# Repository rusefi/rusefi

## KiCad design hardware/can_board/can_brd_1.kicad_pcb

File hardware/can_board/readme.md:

CAN using SN65HVD230

[Forum thread](http://rusefi.com/forum/viewtopic.php?f=4&t=353)

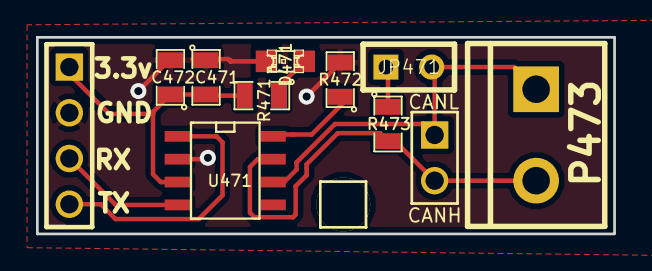
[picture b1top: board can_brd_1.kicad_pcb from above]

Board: 2 copper layers, 32.1 x 10.9 mm, 13 parts (1 on the bottom side), 9 nets.

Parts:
C471: .1uF; SM0805
C472: 4.7uF; SM0805
D471: RED; LED-0805_A
G471: LOGO; LOGO_F
JP471: JUMPER; JUMPER-2
M471: CONN_1; PIN_ARRAY_1
P471: CONN_4; PIN_ARRAY_4x1
P472: CONN_2; PIN_ARRAY_2_A
P473: CONN_2; bornier2
R471: 1k; SM0805
R472: 10k; SM0805
R473: 120; SM0805
U471: SN65HVD230; SO8E

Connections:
/3.3V: C471.2, C472.1, P471.1, R471.2, U471.3
/CANH: P472.2, P473.2, R473.2, U471.7
/CANL: JP471.2, P472.1, P473.1, U471.6
/CAN_RX: P471.3, U471.4
/CAN_TX: P471.4, U471.1
GND: C471.1, C472.2, D471.2, P471.2, R472.2, U471.2
unnamed: D471.1, R471.1
unnamed: JP471.1, R473.1
unnamed: R472.1, U471.8

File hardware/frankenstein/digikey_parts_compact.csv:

### this file was generated by rusEfi bom_builder on Sat Feb 22 11:01:39 CST 2014
### 292 components in 2047 lines of frankenstein.cmp
### 65 kinds of components in input file
### 9 entries in BOM dictionary bom_dictionary_digikey.csv
### 2 entries in ignore list
### no BOM record for 1pin_CONN_1
### no BOM record for LED-0805_GREEN
### no BOM record for LED-0805_LED
### no BOM record for LED-0805_RED
### no BOM record for LED-1206_LED
### no BOM record for MICRO-SDCARD-CONNECTOR-3300060P1_MICRO-SDCARD-CONNECTOR-3300060P1
### no BOM record for OSTVN06A150_CONN_6
### no BOM record for PIN_ARRAY-6X1_CONN_6
### no BOM record for PIN_ARRAY_10X2_CONN_10X2
### no BOM record for PIN_ARRAY_10X2_M_CONN_10X2
### no BOM record for PIN_ARRAY_1_CONN_1
### no BOM record for PIN_ARRAY_2X1_CONN_2
### no BOM record for PIN_ARRAY_2_A_CONN_2
### no BOM record for PIN_ARRAY_2_A_JUMPER
### no BOM record for PIN_ARRAY_3X1_CONN_3
### no BOM record for PIN_ARRAY_3_A_CONN_3
### no BOM record for PIN_ARRAY_4x1_CONN_4
### no BOM record for PIN_ARRAY_5x2_CONN_5X2
### no BOM record for SIL-16_3.5MM_CONN_16
### no BOM record for SIL-2_0R
### no BOM record for SIL-2_CONN_2
### no BOM record for SIL-2_DIODE
### no BOM record for SIL-2_JUMPER
### no BOM record for SIL-2_OPT
### no BOM record for SIL-2_TEST
### no BOM record for SM0805_.1uF
### no BOM record for SM0805_0.01uF
### no BOM record for SM0805_0.1uF
### no BOM record for SM0805_100
### no BOM record for SM0805_1000pF
### no BOM record for SM0805_10K
### no BOM record for SM0805_10k
### no BOM record for SM0805_10uF
### no BOM record for SM0805_120
### no BOM record for SM0805_1500
### no BOM record for SM0805_1K
### no BOM record for SM0805_1M
### no BOM record for SM0805_1uF
### no BOM record for SM0805_20K
### no BOM record for SM0805_2700
### no BOM record for SM0805_4.7uF
### no BOM record for SM0805_4700pF
### no BOM record for SM0805_47pF
### no BOM record for SM0805_500K
### no BOM record for SM0805_5k
### no BOM record for SM0805_LED
### no BOM record for SM1206_LED
### no BOM record for SOD-123_DIODE
### no BOM record for bornier3_CONN_3
### no BOM record for pin_array_10x2_CONN_10X2
### no BOM record for pin_array_3x2_CONN_3X2
### no BOM record for pin_array_4x2_CONN_4X2
### no BOM record for sot23_DOUBLE_SCHOTTKY
### no BOM record for uMAX-uSOP_10_MAX9939




1,670-1190-1-ND,mini USB socket
4,P1.0KACT-ND,some reference
12,P20.0CCT-ND,driver current limiting
1,296-11654-1-ND,CAN driver
12,497-11082-1-ND,12A low-side MOSFET
1,MAX9926UAEE+TCT-ND,VR chip
3,TC4427AVOA-ND,1.5A dual driver
3,497-4943-1-ND,quad op-amp
1,768-1007-1-ND,USB TTL chip

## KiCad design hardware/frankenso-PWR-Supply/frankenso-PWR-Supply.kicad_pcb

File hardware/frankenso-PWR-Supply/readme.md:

https://rusefi.com/forum/viewtopic.php?f=4&t=394

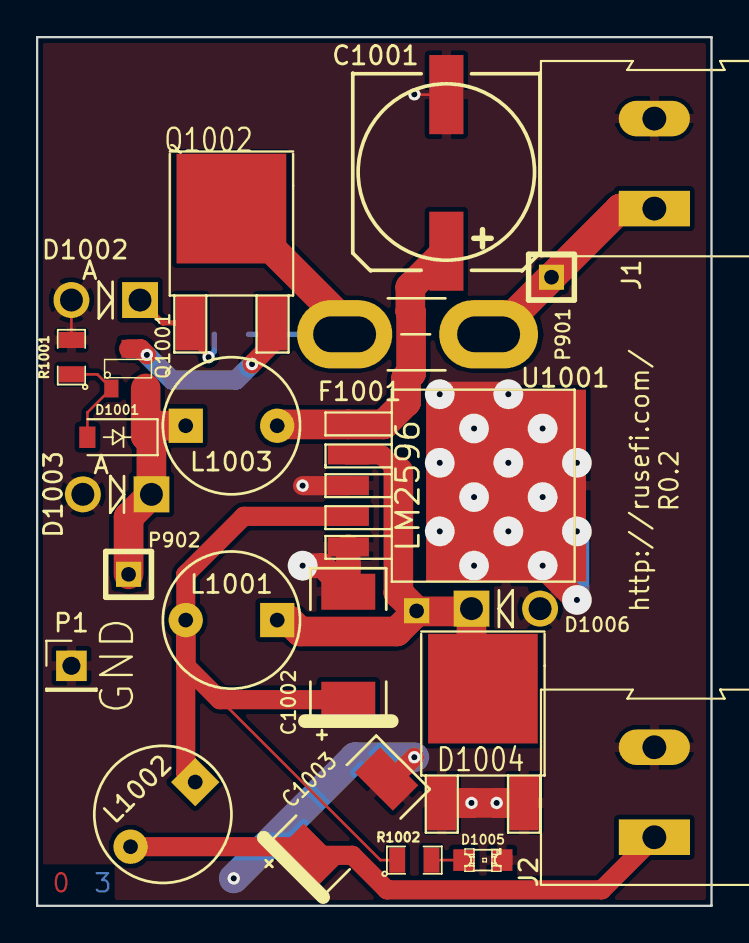
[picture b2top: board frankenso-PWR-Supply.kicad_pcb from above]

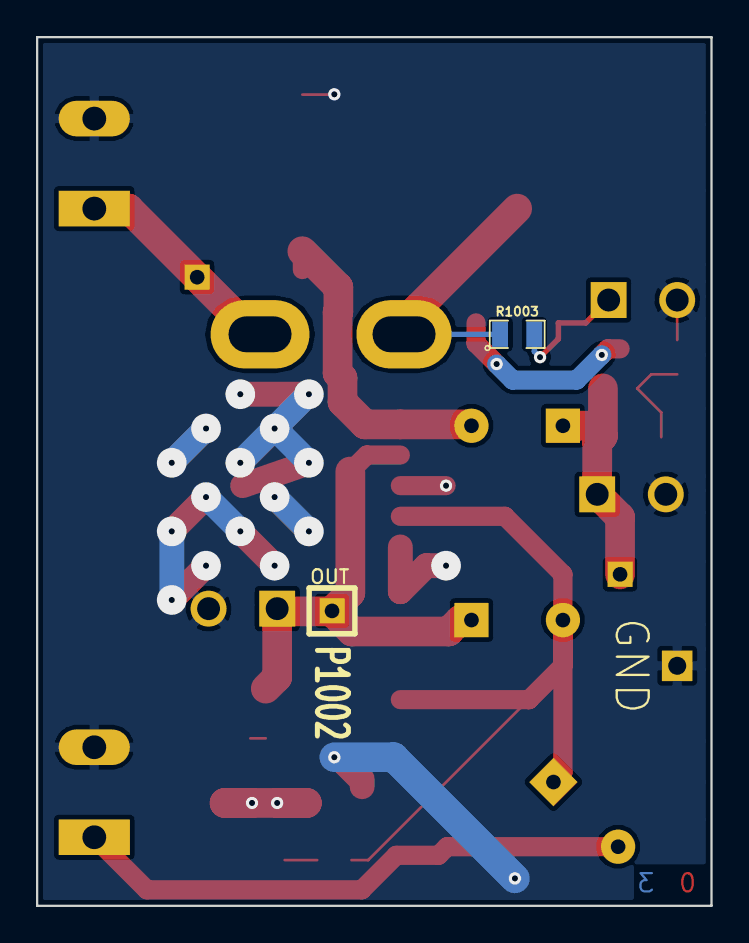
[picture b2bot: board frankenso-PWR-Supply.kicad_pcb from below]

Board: 2 copper layers, 37.5 x 48.3 mm, 25 parts (2 on the bottom side), 12 nets.

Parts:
C1001: 330uF 35V; SMDSVP10
C1002, C1003: 220uF 16V; SM2512
D1001: 7.5V; D_SOD-123
D1002: 17V; Diode_DO-41_SOD81_Vertical_AnodeUp
D1003: 24V; Diode_DO-41_SOD81_Vertical_AnodeUp
D1004: DIODESCH; DPAK2
D1005: LED-grn; LED-0805
D1006: DIODESCH; Diode_DO-41_SOD81_Vertical_AnodeUp
F1001: 1.5A; BladeFuse-Mini
J1, J2: Screw_Terminal_1x02; AK300-2
L1001, L1002, L1003: 68uH; INDUCTOR_V
P1: CONN_1; Pin_Header_Straight_1x01_Pitch2.54mm
P901, P902, P1002: CONN_1; SIL-1
Q1001: 20V; SOT23
Q1002: 200V; DPAK2
R1001: 39k; SM0805
R1002: 1k; SM0805
R1003: 100k; SM0805
U1001: LM2596; DPAK5

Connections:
/5V-REG: C1003.1, J2.1, L1002.2
/FB: C1002.1, L1001.2, L1002.1, R1002.1, U1001.4
/OUT: D1004.2, D1006.1, L1001.1, P1002.1, U1001.2
/VBAT: C1001.1, L1003.2, U1001.1
/Vf: F1001.2, Q1002.2, R1003.1
/Vin: F1001.1, J1.1, P901.1
/Vs1: D1002.1, Q1002.1, R1003.2
/Vs2: Q1001.3, Q1002.3
GND: C1001.2, C1002.2, C1003.2, D1002.2, D1003.2, D1004.1, D1004.3, D1005.2, D1006.2, J1.2, J2.2, P1.1, R1001.2, U1001.3, U1001.5
unnamed: D1001.1, D1003.1, L1003.1, P902.1, Q1001.2
unnamed: D1001.2, Q1001.1, R1001.1
unnamed: D1005.1, R1002.2

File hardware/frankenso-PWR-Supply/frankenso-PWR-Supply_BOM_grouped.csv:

Reference, Quantity, Value, Footprint, Datasheet, MFG,MFG#, VEND1,VEND1#, VEND2,VEND2#, vend1,vend1#, Field4, Field5
C1001 ,1,330uF 35V,SMDSVP10,,unitedchem,EMVY350ADA331MJA0G,DIGI,565-2479-1-ND,,,,
C1002 C1003 ,2,220uF 16V,SM2512,,kemet,T491D227K016AT,DIGI,399-10429-1-ND,sky-macau.com,8702041755,,,
D1001 ,1,7.5V,Diodes_SMD:D_SOD-123,,diodesinc,BZT52C7V5-7-F,DIGI,BZT52C7V5-FDICT-ND,sky-macau.com,5633100308,,,
D1002 ,1,17V,Diode_DO-41_SOD81_Vertical_AnodeUp,,FAIRCHILD,1N5247B,DIGI,1N5247B-ND, ,,,
D1003 ,1,24V,Diode_DO-41_SOD81_Vertical_AnodeUp,,MicroComercial,1N5359B-TP,DIGI,1N5359BTPMSCT-ND,sky-macau.com,0533550982,,,
D1004 ,1,DIODESCH,DPAK2,,VISHAY,VS-50WQ04FN-M3,,,DIGI,VS-50WQ04FN-M3-ND,,
D1005 ,1,LED-grn,LED-0805,,lite-on,LTST-C171GKT,DIGI,160-1423-1-ND,,,,
D1006 ,1,DIODESCH,Diode_DO-41_SOD81_Vertical_AnodeUp,,ONSEMI,MR854G,,sky-macau.com,1438219496,digi,MR854GOS-ND,,
F1001 ,1,1.5A,BladeFuse-Mini,,0R,jumperwire,0R,jumperwire,,,,
J1 J2 ,2,Screw_Terminal_1x02,Connect:AK300-2,
L1001 L1002 L1003 ,3,68uH,INDUCTOR_V,,BOURNS,5800-680-RC,digi,M8288-ND,sky-macau.com,2258345334,,,
P1 ,1,CONN_1,Pin_Headers:Pin_Header_Straight_1x01_Pitch2.54mm,,,,,,dnp,dnp,dnp,dnp
P1002 P901 P902 ,3,CONN_1,SIL-1,,DO NOT POPULATE,DNP,DO NOT POPULATE,DNP,,,,
Q1001 ,1,20V,SOT23,,Vishay,SQ2301ES-T1-GE3,Newark,64T4128,Mouser,78-SQ2301ES-T1_GE3,,,
Q1002 ,1,200V,m-pad-2.1-TO-263AB,,Microchip,DN2625K4-G,digikey,DN2625K4-GCT-ND,,,,
R1001 ,1,39k,SM0805,,ECG,ERA6AEB393V,DIGI,P39KDACT-ND,,,,
R1002 ,1,1k,SM0805,,Panasonic,ERA-6AEB102V,DIGI,P1.0KDACT-ND,,,,
R1003 ,1,100k,SM0805,,ECG,ERA6AEB104V,DIGI,P100KDACT-ND,,,,
U1001 ,1,LM2596,DPAK5,,linear,2596-5.0,DIGI,LM2596S-5.0/NOPB-ND,sky-macau.com,6841999795,,,

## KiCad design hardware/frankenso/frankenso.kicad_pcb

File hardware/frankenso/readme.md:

Our best ECU board

[Wiki manual page](https://rusefi.com/wiki/index.php?title=Manual:Hardware_Frankenso_board)

[Forum thread](https://rusefi.com/forum/viewtopic.php?f=4&t=569)

### For Release Notes see [known_issues.txt](known_issues.txt)

See also comparison [Board Comparison](https://rusefi.com/wiki/index.php?title=Hardware:For_Sale)

iBoms are very cool see https://rusefi.com/docs/ibom/frankenso_latest.html

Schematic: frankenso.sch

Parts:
C23: 1uF; SM0805
C24: 0.1uF; SM0805
D12, D13, D14, D15, D16, D17, D18, D19, D20, D21, D22, D23: DIODESCH; SM0805_jumper
G2: LOGO
JPO1: TEST-LCD; SIL-2
JPO4: TEST-CRK; SIL-2
JPO5: TEST-CAM; SIL-2
P6, P9, P10, P11, P12, P13, P15, P16, P17, P18, P19, P20, P21, P22, P23, P30, P101: CONN_1; SIL-1
P99: 176122-6_2ND; 176122-6_2nd
R99: 1k; SM0805
RV101: 1kpot; TC33X-2-102E
S1: DISPLAY_BL; DISPLAY_4x20_BL
U4: ITEAD_HC-0X; ITEAD_HC-05
U5: SKRHAAE010; joystick_SKRHAAE010
W1, W2, W3, W4, W5, W6, W7, W8, W9, W10, W11, W12, W13, W14, W15, W16, W17, W18, W19, W20, W21, W22, W23, W27, W28, W29, W30, W31, W32, W33, W34, W35, W36, W37, W38, W39, W40, W41, W42, W43, W44, W45, W46, W47, W48, W49, W50, W51, W52, W53, W54, W55, W56, W57, W58, W59, W60, W61, W62, W101: TEST; SM0805_jumper
W63, W64: CONN_1; SIL-1

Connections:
/DD_HIP9011/5V: JPO1.2, W23.1, W49.1; also elsewhere on the board
/DD_HIP9011/CS: P12.1; also elsewhere on the board
/DD_HIP9011/KNOCK0: W30.1; also elsewhere on the board
/DD_HIP9011/KNOCK1: W29.1; also elsewhere on the board
/HD44780_VCC: JPO1.1, S1.2 (VCC), S1.A
/HD44780_VLCD: RV101.3, S1.3 (VLCD), W101.1
/Misc_Vias/3.3V: C23.1, C24.1, U4.12 (VCC); also elsewhere on the board
/Misc_Vias/CAM: JPO5.1; also elsewhere on the board
/Misc_Vias/CRANK: JPO4.1; also elsewhere on the board
/PWR_buck_12V_switcher/5V-REG: W23.2; also elsewhere on the board
/adc_amp_divider/INP1: W55.1; also elsewhere on the board
/adc_amp_divider/INP2: W54.1; also elsewhere on the board
/adc_amp_divider/INP3: W53.1; also elsewhere on the board
/adc_amp_divider/INP4: W52.1; also elsewhere on the board
/adc_amp_divider/INP5: W51.1; also elsewhere on the board
/adc_amp_divider/INP6: W50.1; also elsewhere on the board
/adc_amp_divider/INP7: W47.1; also elsewhere on the board
/adc_amp_divider/INP8: W48.1; also elsewhere on the board
/adc_amp_divider/INP9: W45.1; also elsewhere on the board
/adc_amp_divider/INP10: W46.1; also elsewhere on the board
/adc_amp_divider/INP11: W43.1; also elsewhere on the board
/adc_amp_divider/INP12: W44.1; also elsewhere on the board
/can_brd_1/CANH: W33.1; also elsewhere on the board
/can_brd_1/CANL: W34.1; also elsewhere on the board
/can_brd_1/CAN_RX: P15.1; also elsewhere on the board
/cps_vrs_io_1/CAM+: P99.24; also elsewhere on the board
/cps_vrs_io_1/CAM-: P99.32; also elsewhere on the board
/cps_vrs_io_1/CRK2+: P99.23; also elsewhere on the board
/cps_vrs_io_1/CRK2-: P99.31; also elsewhere on the board
/hi-lo/12V: D12.2 (K), D13.2 (K), D14.2 (K), D15.2 (K), D16.2 (K), D17.2 (K), D18.2 (K), D19.2 (K), D20.2 (K), D21.2 (K), D22.2 (K), D23.2 (K), W2.1; also elsewhere on the board
/hi-lo/HL1: W6.1; also elsewhere on the board
/hi-lo/HL2: W8.1; also elsewhere on the board
/hi-lo/HL3: W7.1; also elsewhere on the board
/hi-lo/HL4: W13.1; also elsewhere on the board
/hi-lo/HL5: W9.1; also elsewhere on the board
/hi-lo/HL6: W12.1; also elsewhere on the board
/inj_12ch/INJ-01_2: W38.1; also elsewhere on the board
/inj_12ch/INJ-02: W37.1; also elsewhere on the board
/inj_12ch/INJ-03: W36.1; also elsewhere on the board
/inj_12ch/INJ-03_5V: P23.1; also elsewhere on the board
/inj_12ch/INJ-04: W35.1; also elsewhere on the board
/inj_12ch/INJ-05: W57.1; also elsewhere on the board
/inj_12ch/INJ-06: W58.1; also elsewhere on the board
/inj_12ch/INJ-07: W59.1; also elsewhere on the board
/inj_12ch/INJ-08: W60.1; also elsewhere on the board
/inj_12ch/INJ-09: W61.1; also elsewhere on the board
/inj_12ch/INJ-10: W62.1; also elsewhere on the board
/inj_12ch/INJ-11: D22.1 (A), P99.51, W63.1; also elsewhere on the board
/inj_12ch/INJ-12: D23.1 (A), P99.64, W64.1; also elsewhere on the board
/stm32f407_board/BOOT0: P30.1; also elsewhere on the board
/stm32f407_board/PA5: JPO4.2; also elsewhere on the board
/stm32f407_board/PA15: P11.1; also elsewhere on the board
/stm32f407_board/PB1: P13.1; also elsewhere on the board
/stm32f407_board/PB10: S1.14 (D7); also elsewhere on the board
/stm32f407_board/PC6: JPO5.2; also elsewhere on the board
/stm32f407_board/PC8: U5.6 (B); also elsewhere on the board
/stm32f407_board/PC10: U4.2 (UART_RX); also elsewhere on the board
/stm32f407_board/PC11: U4.1 (UART_TX); also elsewhere on the board
/stm32f407_board/PC12: P16.1; also elsewhere on the board
/stm32f407_board/PD0: P17.1; also elsewhere on the board
/stm32f407_board/PD1: P18.1; also elsewhere on the board
/stm32f407_board/PD2: P19.1; also elsewhere on the board
/stm32f407_board/PD3: P20.1; also elsewhere on the board
/stm32f407_board/PD5: P21.1; also elsewhere on the board
/stm32f407_board/PD6: P22.1; also elsewhere on the board
/stm32f407_board/PD8: U5.1 (A); also elsewhere on the board
/stm32f407_board/PD9: U5.3 (C); also elsewhere on the board
/stm32f407_board/PD10: U5.2 (Center); also elsewhere on the board
/stm32f407_board/PD11: U5.4 (D); also elsewhere on the board
/stm32f407_board/PE7: S1.4 (RS); also elsewhere on the board
/stm32f407_board/PE9: S1.6 (CS); also elsewhere on the board
/stm32f407_board/PE11: S1.11 (D4); also elsewhere on the board
/stm32f407_board/PE13: S1.12 (D5); also elsewhere on the board
/stm32f407_board/PE15: S1.13 (D6); also elsewhere on the board
/thermocouple1//CS: P101.1; also elsewhere on the board
/thermocouple2//CS: P10.1; also elsewhere on the board
/thermocouple3//CS: P6.1; also elsewhere on the board
/thermocouple4//CS: P9.1; also elsewhere on the board
GND: C23.2, C24.2, R99.1, S1.1 (GND), S1.5 (R/W), S1.K, U4.13 (GND), U4.21 (GND), U4.22 (GND), U5.5 (Com), W39.1, W40.1, W41.1, W42.1; also elsewhere on the board
unnamed: P99.58, W52.2
unnamed: P99.39, W39.2
unnamed: P99.52, W40.2
unnamed: P99.40, W41.2
unnamed: P99.53, W42.2
unnamed: P99.41, W43.2
unnamed: P99.54, W44.2
unnamed: P99.42, W45.2
unnamed: P99.55, W46.2
unnamed: P99.43, W47.2
unnamed: P99.56, W48.2
unnamed: P99.44, W49.2
unnamed: P99.57, W50.2
unnamed: P99.45, W51.2
unnamed: P99.46, W53.2
unnamed: P99.59, W54.2
unnamed: P99.47, W55.2
unnamed: P99.60, W56.2
unnamed: P99.12, W2.2
unnamed: R99.2, RV101.1, RV101.2, W101.2
unnamed: P99.34, W30.2
unnamed: P99.35, W32.2
unnamed: P99.26, W29.2
unnamed: P99.36, W34.2
unnamed: P99.27, W31.2
unnamed: D13.1 (A), P99.37, W36.2
unnamed: D15.1 (A), P99.38, W38.2
unnamed: D12.1 (A), P99.29, W35.2
unnamed: D20.1 (A), P99.50, W61.2
unnamed: D17.1 (A), P99.61, W58.2
unnamed: D19.1 (A), P99.62, W60.2
unnamed: D21.1 (A), P99.63, W62.2
unnamed: P99.11, W21.2
unnamed: P99.21, W20.2
unnamed: P99.22, W22.2
unnamed: D14.1 (A), P99.30, W37.2
unnamed: D16.1 (A), P99.48, W57.2
unnamed: D18.1 (A), P99.49, W59.2
unnamed: P99.25, W27.2
unnamed: P99.33, W28.2
unnamed: P99.28, W33.2
unnamed: P99.17, W12.2
unnamed: P99.3, W5.2
unnamed: P99.14, W6.2
unnamed: P99.4, W7.2
unnamed: P99.15, W8.2
unnamed: P99.5, W9.2
unnamed: P99.16, W10.2
unnamed: P99.6, W11.2
unnamed: P99.13, W4.2
unnamed: P99.7, W13.2
unnamed: P99.18, W14.2
unnamed: P99.8, W15.2
unnamed: P99.19, W16.2
unnamed: P99.9, W17.2
unnamed: P99.20, W18.2
unnamed: P99.10, W19.2
unnamed: P99.1, W1.2
unnamed: P99.2, W3.2

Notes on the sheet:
rusEfi
The JP1 jumper is needed because we cannot feed the screen via USB - we would need to disconnect it while the board is on a bench
pg 3
pg 5
pg 7
pg 6
pg 2
pg 8
pg 4
pg 11
pg 9
pg 10
pg 12
pg 13
pg 14

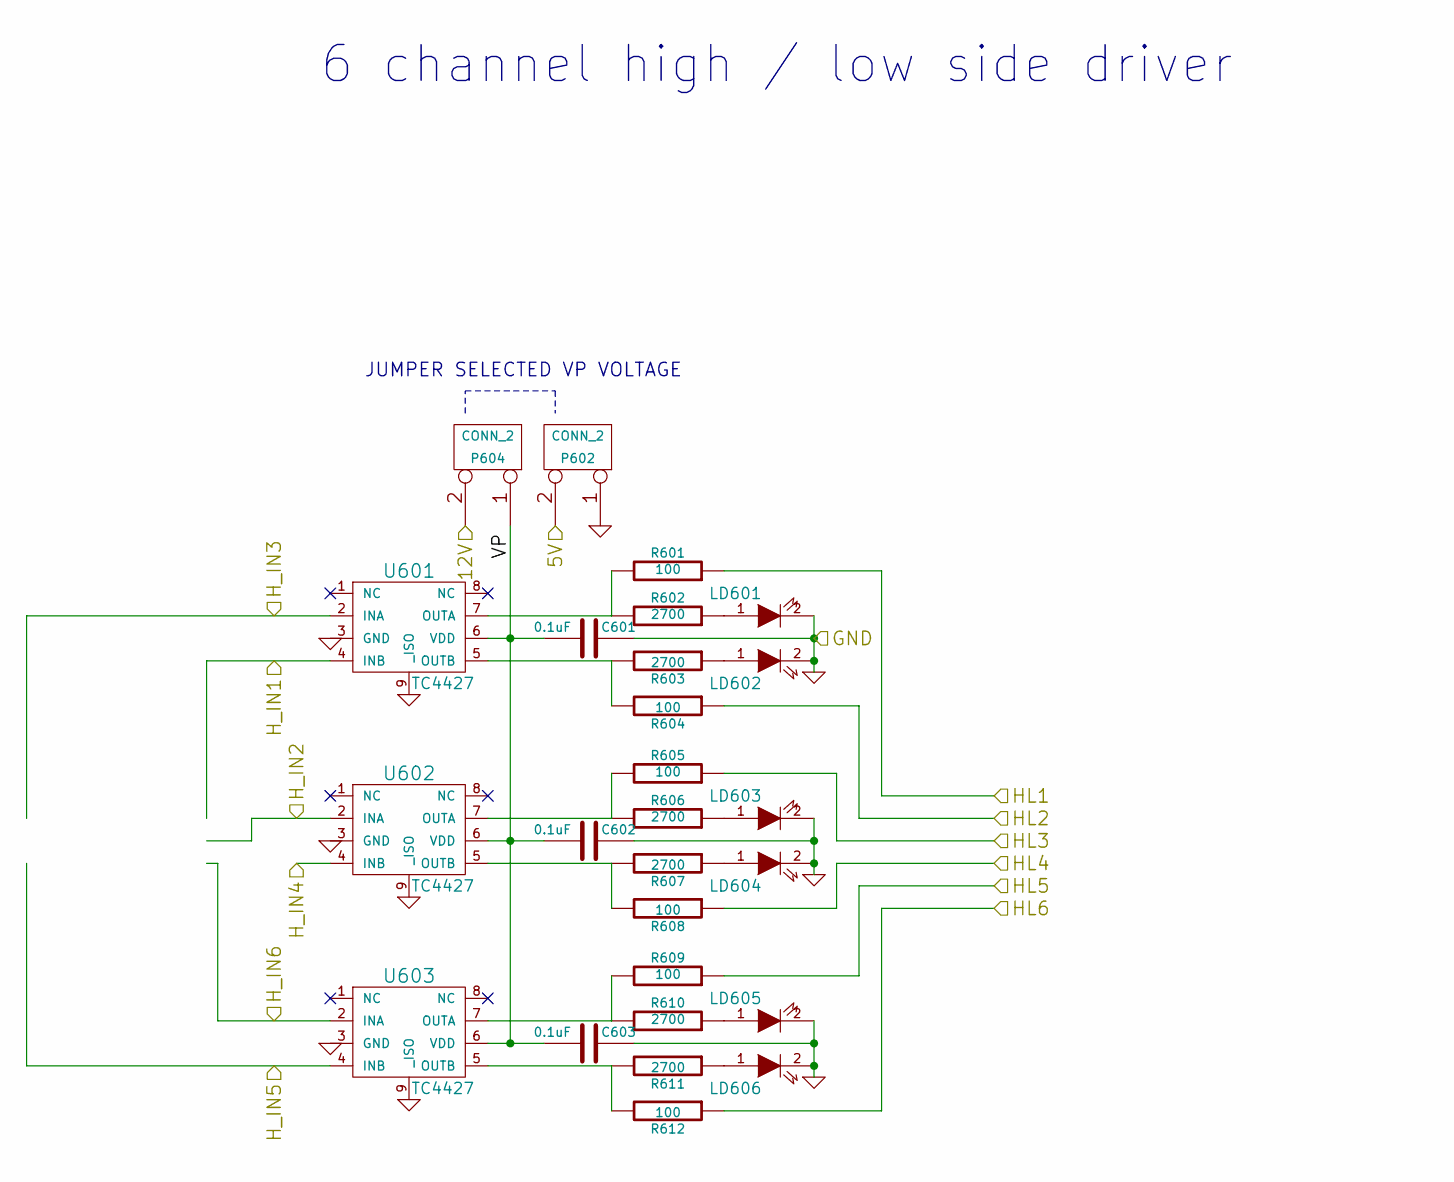
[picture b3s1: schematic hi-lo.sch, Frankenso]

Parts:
C601, C602, C603: 0.1uF; SM0805
LD601, LD602, LD603, LD604, LD605, LD606: LED-blu; LED-0805
P602, P604: CONN_2; SIL-2
R601, R604, R605, R608, R609, R612: 100; SM0805
R602, R603, R606, R607, R610, R611: 2700; SM0805
U601, U602, U603: TC4427; SOIC8-DFN

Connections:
/DD_HIP9011/5V: P602.2 (PM); also elsewhere on the board
/hi-lo/12V: P604.2 (PM); also elsewhere on the board
/hi-lo/HL1: R601.1; also elsewhere on the board
/hi-lo/HL2: R604.1; also elsewhere on the board
/hi-lo/HL3: R605.1; also elsewhere on the board
/hi-lo/HL4: R608.1; also elsewhere on the board
/hi-lo/HL5: R609.1; also elsewhere on the board
/hi-lo/HL6: R612.1; also elsewhere on the board
/hi-lo/H_IN1: U601.4 (INB); also elsewhere on the board
/hi-lo/H_IN2: U602.2 (INA); also elsewhere on the board
/hi-lo/H_IN3: U601.2 (INA); also elsewhere on the board
/hi-lo/H_IN4: U602.4 (INB); also elsewhere on the board
/hi-lo/H_IN5: U603.4 (INB); also elsewhere on the board
/hi-lo/H_IN6: U603.2 (INA); also elsewhere on the board
/hi-lo/VP: C601.2, C602.2, C603.2, P604.1, U601.6 (VDD), U602.6 (VDD), U603.6 (VDD)
GND: C601.1, C602.1, C603.1, LD601.2 (K), LD602.2 (K), LD603.2 (K), LD604.2 (K), LD605.2 (K), LD606.2 (K), P602.1, U601.3 (GND), U601.9 (_ISO), U602.3 (GND), U602.9 (_ISO), U603.3 (GND), U603.9 (_ISO); also elsewhere on the board
unnamed: LD601.1 (A), R602.1
unnamed: LD603.1 (A), R606.1
unnamed: LD604.1 (A), R607.1
unnamed: LD602.1 (A), R603.1
unnamed: R601.2, R602.2, U601.7 (OUTA)
unnamed: R605.2, R606.2, U602.7 (OUTA)
unnamed: LD605.1 (A), R610.1
unnamed: R609.2, R610.2, U603.7 (OUTA)
unnamed: R607.2, R608.2, U602.5 (OUTB)
unnamed: R611.2, R612.2, U603.5 (OUTB)
unnamed: LD606.1 (A), R611.1
unnamed: R603.2, R604.2, U601.5 (OUTB)

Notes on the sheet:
6 channel high / low side driver
JUMPER SELECTED VP VOLTAGE

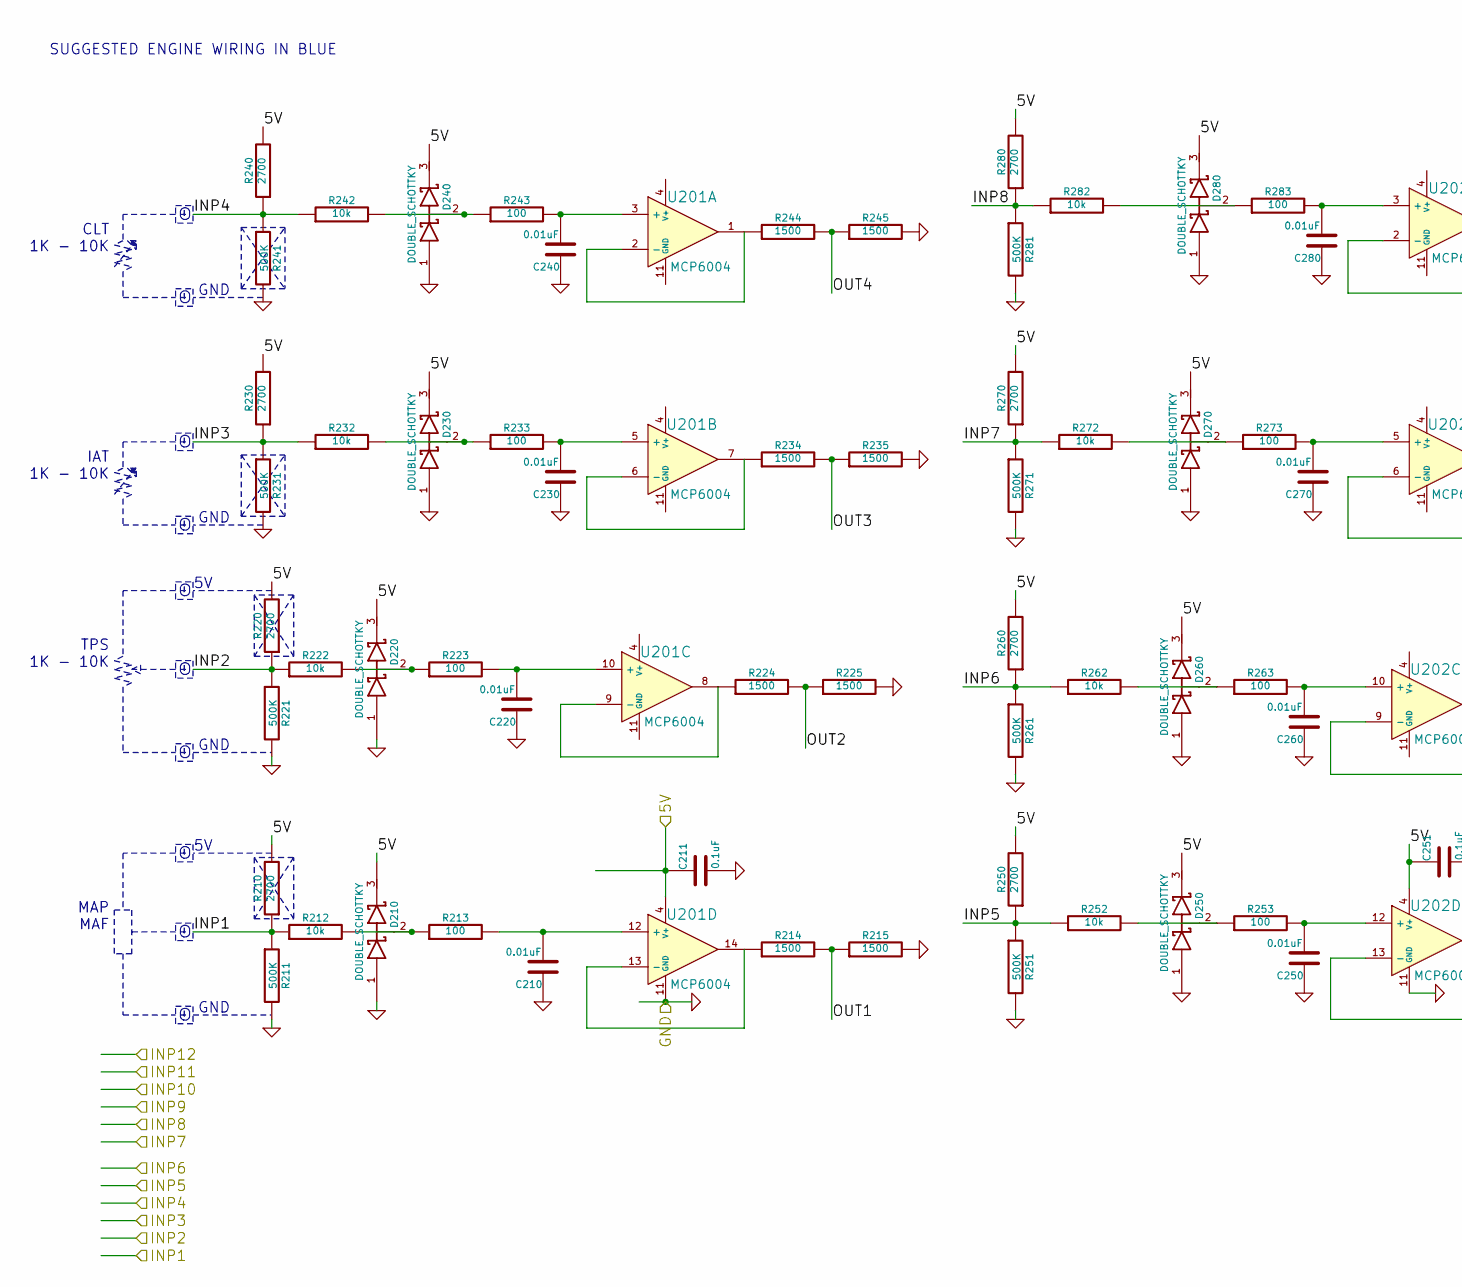
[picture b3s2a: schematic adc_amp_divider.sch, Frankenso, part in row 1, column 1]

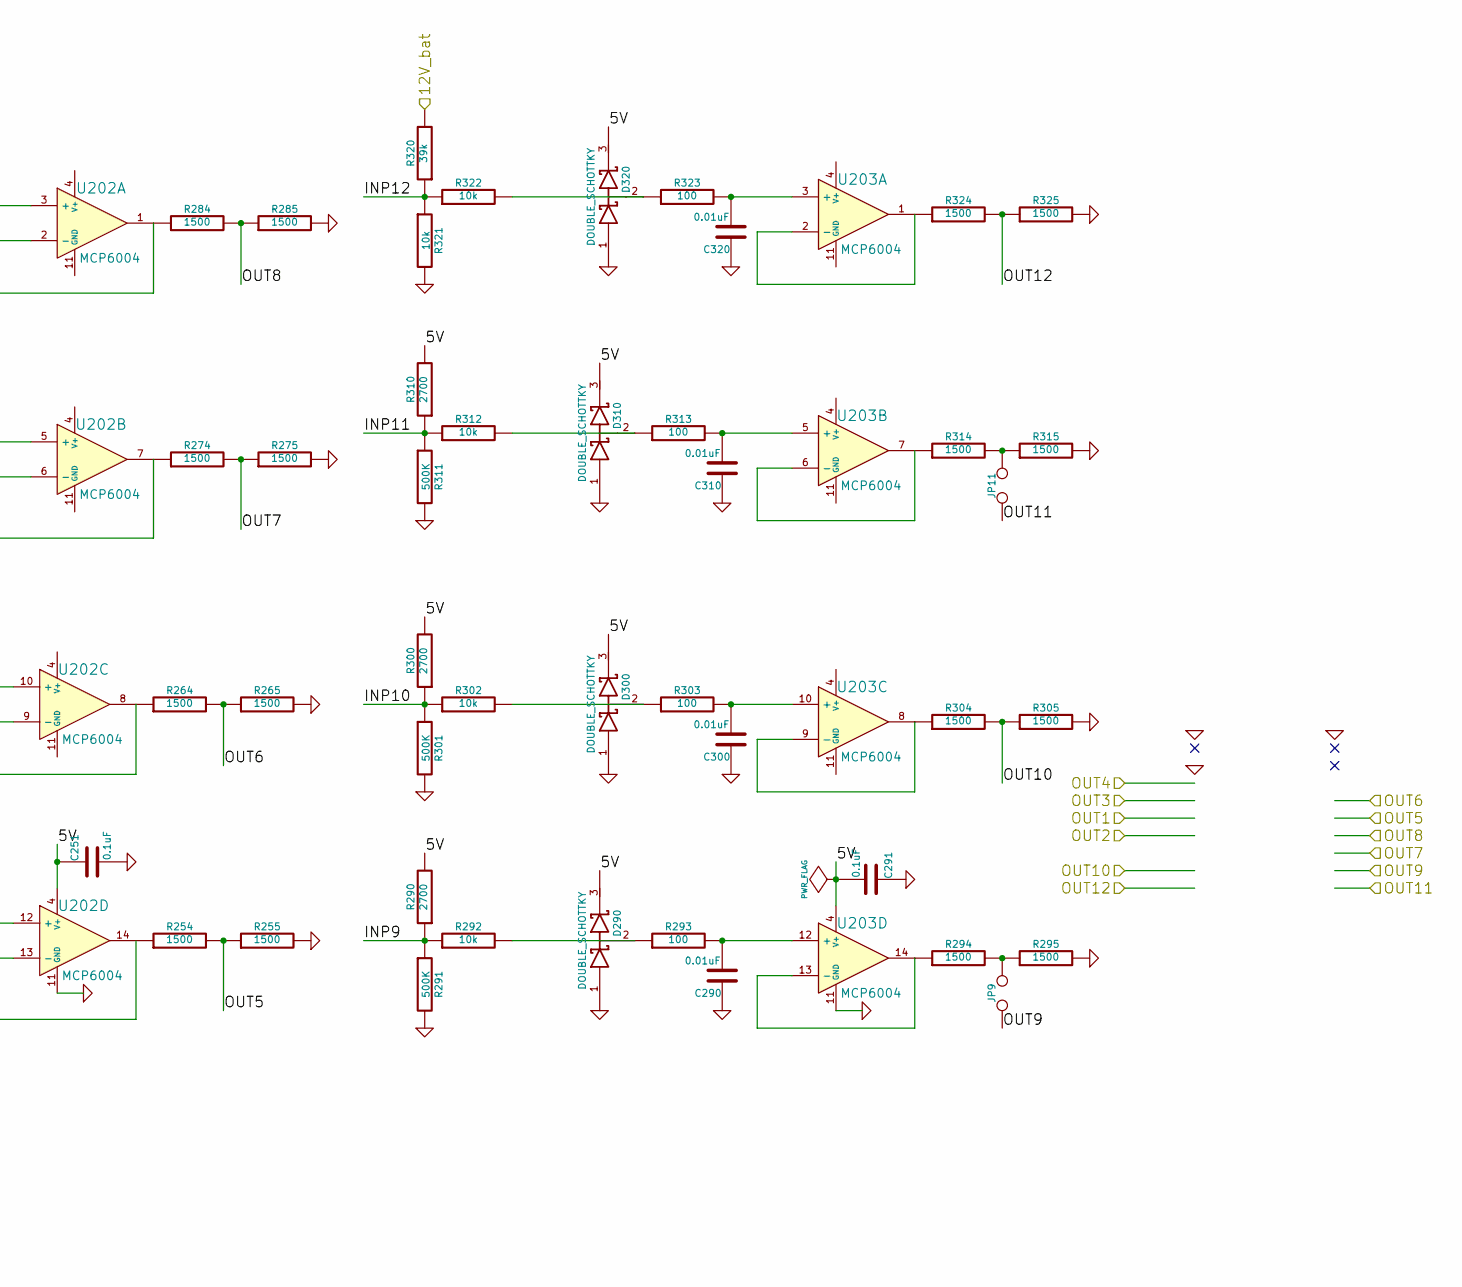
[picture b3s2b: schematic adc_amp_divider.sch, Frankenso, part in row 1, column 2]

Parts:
C210, C220, C230, C240, C250, C260, C270, C280, C290, C300, C310, C320: 0.01uF; SM0805
C211, C251, C291: 0.1uF; SM0805
D210, D220, D230, D240, D250, D260, D270, D280, D290, D300, D310, D320: DOUBLE_SCHOTTKY; sot23
JP9, JP11: TEST-AN; SIL-2
R210, R220, R230, R240, R250, R260, R270, R280, R290, R300, R310: 2700; SM0805
R211, R221, R231, R241, R251, R261, R271, R281, R291, R301, R311: 500K; SM0805
R212, R222, R232, R242, R252, R262, R272, R282, R292, R302, R312, R321, R322: 10k; SM0805
R213, R223, R233, R243, R253, R263, R273, R283, R293, R303, R313, R323: 100; SM0805
R214, R215, R224, R225, R234, R235, R244, R245, R254, R255, R264, R265, R274, R275, R284, R285, R294, R295, R304, R305, R314, R315, R324, R325: 1500; SM0805
R320: 39k; SM0805
U201, U202, U203: MCP6004; SO14N

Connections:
/DD_HIP9011/5V: C211.1, C251.1, C291.2, D210.3 (cathode), D220.3 (cathode), D230.3 (cathode), D240.3 (cathode), D250.3 (cathode), D260.3 (cathode), D270.3 (cathode), D280.3 (cathode), D290.3 (cathode), D300.3 (cathode), D310.3 (cathode), D320.3 (cathode), R210.2, R220.2, R230.2, R240.2, R250.2, R260.2, R270.2, R280.2, R290.2, R300.2, R310.2, U201.4 (V+), U202.4 (V+), U203.4 (V+); also elsewhere on the board
/adc_amp_divider/INP1: R210.1, R211.1, R212.1; also elsewhere on the board
/adc_amp_divider/INP2: R220.1, R221.1, R222.1; also elsewhere on the board
/adc_amp_divider/INP3: R230.1, R231.1, R232.1; also elsewhere on the board
/adc_amp_divider/INP4: R240.1, R241.1, R242.1; also elsewhere on the board
/adc_amp_divider/INP5: R250.1, R251.1, R252.1; also elsewhere on the board
/adc_amp_divider/INP6: R260.1, R261.1, R262.1; also elsewhere on the board
/adc_amp_divider/INP7: R270.1, R271.1, R272.1; also elsewhere on the board
/adc_amp_divider/INP8: R280.1, R281.1, R282.1; also elsewhere on the board
/adc_amp_divider/INP9: R290.1, R291.1, R292.1; also elsewhere on the board
/adc_amp_divider/INP10: R300.1, R301.1, R302.1; also elsewhere on the board
/adc_amp_divider/INP11: R310.1, R311.1, R312.1; also elsewhere on the board
/adc_amp_divider/INP12: R320.1, R321.1, R322.1; also elsewhere on the board
/adc_amp_divider/OUT1: R214.2, R215.1; also elsewhere on the board
/adc_amp_divider/OUT2: R224.2, R225.1; also elsewhere on the board
/adc_amp_divider/OUT3: R234.2, R235.1; also elsewhere on the board
/adc_amp_divider/OUT4: R244.2, R245.1; also elsewhere on the board
/adc_amp_divider/OUT5: R254.2, R255.1; also elsewhere on the board
/adc_amp_divider/OUT6: R264.2, R265.1; also elsewhere on the board
/adc_amp_divider/OUT7: R274.2, R275.1; also elsewhere on the board
/adc_amp_divider/OUT8: R284.2, R285.1; also elsewhere on the board
/adc_amp_divider/OUT9: JP9.1; also elsewhere on the board
/adc_amp_divider/OUT10: R304.2, R305.1; also elsewhere on the board
/adc_amp_divider/OUT11: JP11.1; also elsewhere on the board
/adc_amp_divider/OUT12: R324.2, R325.1; also elsewhere on the board
/hi-lo/12V: R320.2; also elsewhere on the board
GND: C210.1, C211.2, C220.1, C230.1, C240.1, C250.1, C251.2, C260.1, C270.1, C280.1, C290.1, C291.1, C300.1, C310.1, C320.1, D210.1 (Anode), D220.1 (Anode), D230.1 (Anode), D240.1 (Anode), D250.1 (Anode), D260.1 (Anode), D270.1 (Anode), D280.1 (Anode), D290.1 (Anode), D300.1 (Anode), D310.1 (Anode), D320.1 (Anode), R211.2, R215.2, R221.2, R225.2, R231.2, R235.2, R241.2, R245.2, R251.2, R255.2, R261.2, R265.2, R271.2, R275.2, R281.2, R285.2, R291.2, R295.2, R301.2, R305.2, R311.2, R315.2, R321.2, R325.2, U201.11 (GND), U202.11 (GND), U203.11 (GND); also elsewhere on the board
unnamed: D230.2 (AK), R232.2, R233.1
unnamed: C260.2, R263.2, U202.10 (+)
unnamed: D260.2 (AK), R262.2, R263.1
unnamed: R224.1, U201.8, U201.9 (-)
unnamed: R214.1, U201.13 (-), U201.14
unnamed: R314.1, U203.6 (-), U203.7
unnamed: R324.1, U203.1, U203.2 (-)
unnamed: C310.2, R313.2, U203.5 (+)
unnamed: C320.2, R323.2, U203.3 (+)
unnamed: JP9.2, R294.2, R295.1
unnamed: JP11.2, R314.2, R315.1
unnamed: C250.2, R253.2, U202.12 (+)
unnamed: D320.2 (AK), R322.2, R323.1
unnamed: D310.2 (AK), R312.2, R313.1
unnamed: R234.1, U201.6 (-), U201.7
unnamed: C220.2, R223.2, U201.10 (+)
unnamed: D220.2 (AK), R222.2, R223.1
unnamed: C230.2, R233.2, U201.5 (+)
unnamed: R244.1, U201.1, U201.2 (-)
unnamed: C210.2, R213.2, U201.12 (+)
unnamed: D210.2 (AK), R212.2, R213.1
unnamed: R254.1, U202.13 (-), U202.14
unnamed: C280.2, R283.2, U202.3 (+)
unnamed: D280.2 (AK), R282.2, R283.1
unnamed: D250.2 (AK), R252.2, R253.1
unnamed: R264.1, U202.8, U202.9 (-)
unnamed: R274.1, U202.6 (-), U202.7
unnamed: C240.2, R243.2, U201.3 (+)
unnamed: C270.2, R273.2, U202.5 (+)
unnamed: R284.1, U202.1, U202.2 (-)
unnamed: R304.1, U203.8, U203.9 (-)
unnamed: D240.2 (AK), R242.2, R243.1
unnamed: R294.1, U203.13 (-), U203.14
unnamed: C290.2, R293.2, U203.12 (+)
unnamed: C300.2, R303.2, U203.10 (+)
unnamed: D300.2 (AK), R302.2, R303.1
unnamed: D290.2 (AK), R292.2, R293.1
unnamed: D270.2 (AK), R272.2, R273.1

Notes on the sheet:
CLT 1K - 10K
SUGGESTED ENGINE WIRING IN BLUE
IAT 1K - 10K
GND
TPS 1K - 10K
MAP MAF

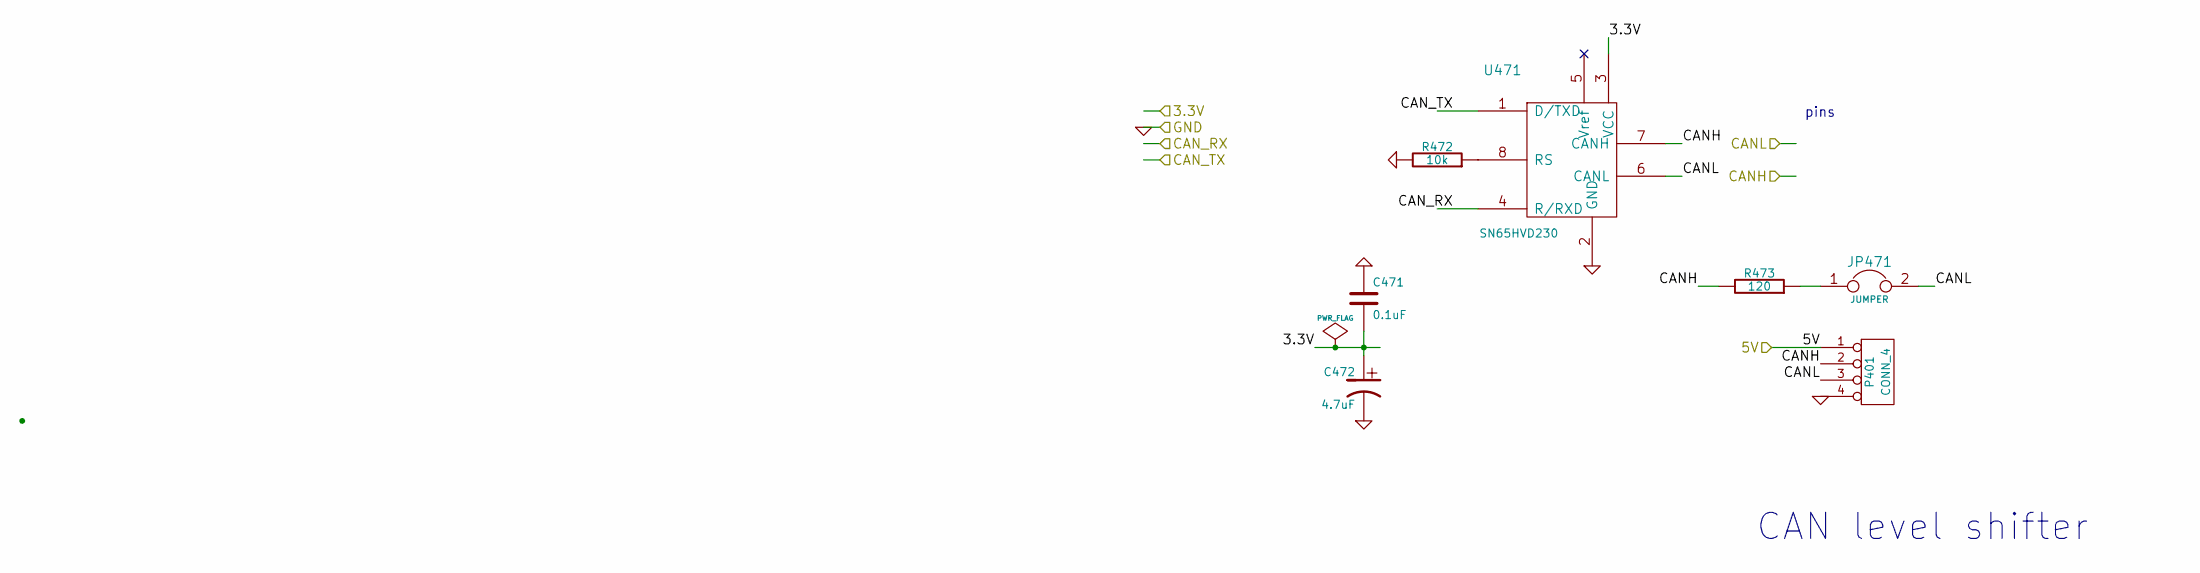
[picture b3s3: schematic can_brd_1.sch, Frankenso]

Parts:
C471: 0.1uF; SM0805
C472: 4.7uF; SM0805
JP471: JUMPER; JUMPER-2
P401: CONN_4; SIL-4
R472: 10k; SM0805
R473: 120; SM0805
U471: SN65HVD230; SO8E

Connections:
/DD_HIP9011/5V: P401.1; also elsewhere on the board
/Misc_Vias/3.3V: C471.2, C472.1, U471.3 (VCC); also elsewhere on the board
/can_brd_1/CANH: P401.2, R473.2, U471.7 (CANH); also elsewhere on the board
/can_brd_1/CANL: JP471.2, P401.3, U471.6 (CANL); also elsewhere on the board
/can_brd_1/CAN_RX: U471.4 (R/RXD); also elsewhere on the board
/can_brd_1/CAN_TX: U471.1 (D/TXD); also elsewhere on the board
GND: C471.1, C472.2, P401.4, R472.2, U471.2 (GND); also elsewhere on the board
unnamed: JP471.1, R473.1
unnamed: R472.1, U471.8 (RS)

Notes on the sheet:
CAN level shifter
pins
